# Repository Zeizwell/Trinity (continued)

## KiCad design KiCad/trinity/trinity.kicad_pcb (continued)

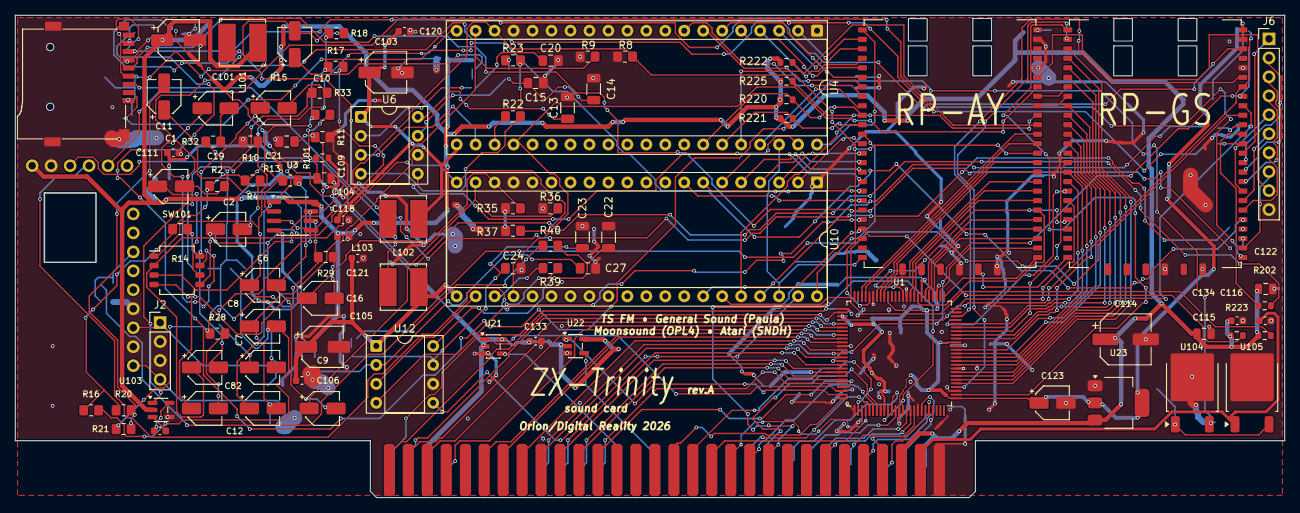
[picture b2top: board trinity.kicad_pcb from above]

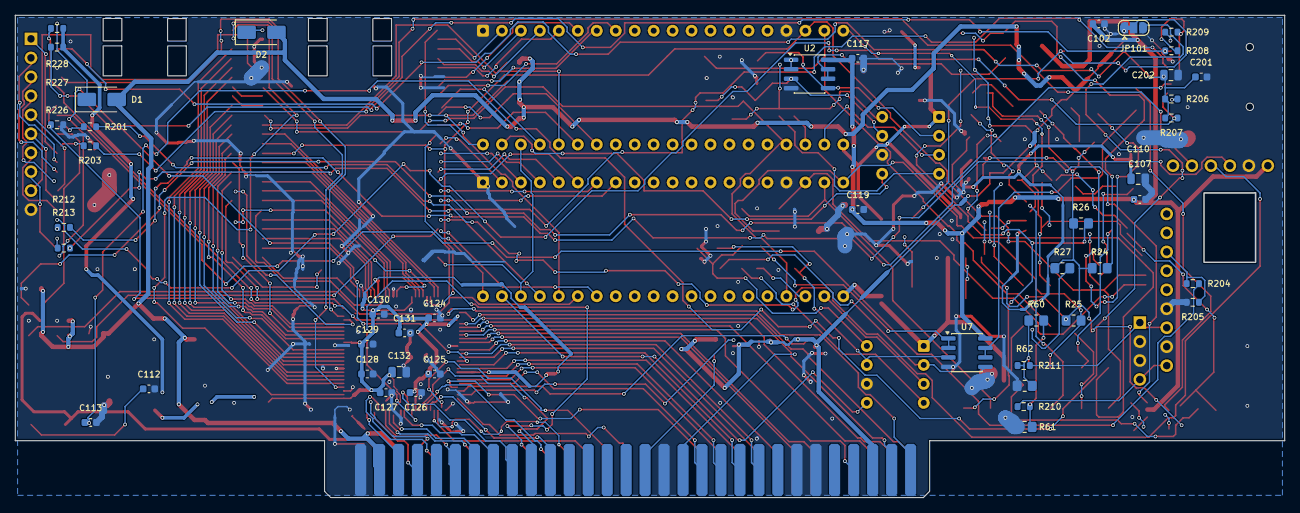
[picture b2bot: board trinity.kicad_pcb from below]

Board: 2 copper layers, 170.0 x 64.6 mm, 142 parts (45 on the bottom side), 193 nets.

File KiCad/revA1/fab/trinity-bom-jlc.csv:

Comment,Designator,Footprint,LCSC
10u,"C1,C2,C6,C7,C8,C9,C10,C11,C12,C16,C19,C21,C82,C83",CP_Elec_4x5.4,C213487
47u,"C101,C103,C105",CP_Elec_5x5.4,C72515
100n,"C102,C117,C119,C124,C125,C126,C127,C128,C129,C130,C131,C201,C104,C106,C111,C118,C120,C121,C133,C134",C_0603_1608Metric,C14663
2.2u,C107,C_0603_1608Metric,C23630
1u,C108,C_0603_1608Metric,C15849
10u,"C110,C132,C202,C109,C115,C122",C_0805_2012Metric,C15850
100u/16V,C114,CP_Elec_6.3x7.7,C72476
22u,C123,CP_Elec_4x5.4,C72502
10u/16V X5R,"C13,C14,C22,C23",C_1206_3216Metric,C13585
2.2n,"C20,C27",C_0805_2012Metric_Pad1.18x1.45mm_HandSolder,C28260
100n,"C4,C15,C24",C_0805_2012Metric_Pad1.18x1.45mm_HandSolder,C49678
SS14,"D1,D2",D_SMA,C2480
27u,"L101,L102,L103",L_Bourns_SRN6045TA,C168081
10,R101,R_0603_1608Metric,C22859
0,R11,R_0805_2012Metric_Pad1.20x1.40mm_HandSolder,C17477
24k,"R13,R14,R28,R29",R_0805_2012Metric_Pad1.20x1.40mm_HandSolder,C17575
82k,"R2,R4,R32,R33",R_0805_2012Metric_Pad1.20x1.40mm_HandSolder,C17840
33,"R201,R203,R212,R213,R202",R_0603_1608Metric,C23140
1k,"R204,R210,R211,R226",R_0603_1608Metric,C21190
10k,"R206,R207,R208,R209,R227,R228,R220,R221,R222,R223,R224,R225",R_0603_1608Metric,C25804
1k,"R22,R39",R_0805_2012Metric_Pad1.20x1.40mm_HandSolder,C17513
470,"R23,R40",R_0805_2012Metric_Pad1.20x1.40mm_HandSolder,C17710
10k,"R24,R18,R20,R21",R_0805_2012Metric_Pad1.20x1.40mm_HandSolder,C17414
10K,"R25,R60,R15",R_0805_2012Metric_Pad1.20x1.40mm_HandSolder,C17414
47k,"R26,R27,R61,R62,R16,R17",R_0805_2012Metric_Pad1.20x1.40mm_HandSolder,C17713
3.3k,"R8,R9,R10,R35,R36,R37",R_0805_2012Metric_Pad1.20x1.40mm_HandSolder,C26010
NARROW,SW101,SW_DIP_SPSTx04_Slide_Omron_A6H-4101_W6.15mm_P1.27mm,C397291
TPS60400,U103,SOT-23-5,C9839
LM358D,"U2,U7",SOIC-8_3.9x4.9mm_P1.27mm,C7950
74LVC1G125,"U21,U22",SOT-23-5,C23654
AMS1117-3.3,U23,SOT-223-3_TabPin2,C6186
NJM4580,U3,SOIC-8_3.9x4.9mm_P1.27mm,C3000516

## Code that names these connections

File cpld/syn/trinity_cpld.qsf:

# Ножки - из KiCad/trinity/gen/cpld_gen.py
set_global_assignment -name FAMILY MAX3000A
set_global_assignment -name DEVICE "EPM3128ATC100-10"
set_global_assignment -name TOP_LEVEL_ENTITY trinity_cpld
set_global_assignment -name VERILOG_FILE ../rtl/top.v
set_global_assignment -name SDC_FILE clocks.sdc
set_global_assignment -name MAX7000_DEVICE_IO_STANDARD "3.3-V LVTTL"
set_global_assignment -name RESERVE_ALL_UNUSED_PINS "AS INPUT TRI-STATED"
set_location_assignment PIN_87 -to clk
set_location_assignment PIN_13 -to a[0]
set_location_assignment PIN_16 -to a[1]
set_location_assignment PIN_19 -to a[2]
set_location_assignment PIN_21 -to a[3]
set_location_assignment PIN_40 -to a[4]
set_location_assignment PIN_37 -to a[5]
set_location_assignment PIN_36 -to a[6]
set_location_assignment PIN_32 -to a[7]
set_location_assignment PIN_44 -to a[8]
set_location_assignment PIN_45 -to a[9]
set_location_assignment PIN_46 -to a[10]
set_location_assignment PIN_47 -to a[11]
set_location_assignment PIN_5 -to a[12]
set_location_assignment PIN_6 -to a[13]
set_location_assignment PIN_1 -to a[14]
set_location_assignment PIN_2 -to a[15]
set_location_assignment PIN_9 -to d[0]
set_location_assignment PIN_10 -to d[1]
set_location_assignment PIN_12 -to d[2]
set_location_assignment PIN_20 -to d[3]
set_location_assignment PIN_22 -to d[4]
set_location_assignment PIN_17 -to d[5]
set_location_assignment PIN_14 -to d[6]
set_location_assignment PIN_7 -to d[7]
set_location_assignment PIN_8 -to n_dos
set_location_assignment PIN_23 -to n_iorqge
set_location_assignment PIN_24 -to n_csromce_oe
set_location_assignment PIN_25 -to n_mreq
set_location_assignment PIN_27 -to n_iorq
set_location_assignment PIN_28 -to n_rd
set_location_assignment PIN_29 -to n_wr
set_location_assignment PIN_30 -to n_rst
set_location_assignment PIN_31 -to n_iodos
set_location_assignment PIN_35 -to n_wait
set_location_assignment PIN_41 -to n_m1
set_location_assignment PIN_42 -to csrom
set_location_assignment PIN_52 -to gs_c[0]
set_location_assignment PIN_54 -to gs_c[1]
set_location_assignment PIN_55 -to gs_c[2]
set_location_assignment PIN_56 -to gs_c[3]
set_location_assignment PIN_57 -to gs_c[4]
set_location_assignment PIN_58 -to gs_c[5]
set_location_assignment PIN_60 -to gs_wr
set_location_assignment PIN_61 -to gs_d[0]
set_location_assignment PIN_63 -to gs_d[1]
set_location_assignment PIN_64 -to gs_d[2]
set_location_assignment PIN_67 -to gs_d[3]
set_location_assignment PIN_68 -to gs_d[4]
set_location_assignment PIN_69 -to gs_d[5]
set_location_assignment PIN_70 -to gs_d[6]
set_location_assignment PIN_71 -to gs_d[7]
set_location_assignment PIN_72 -to gs_rd
set_location_assignment PIN_75 -to gs_rdy
set_location_assignment PIN_76 -to ay_d[0]
set_location_assignment PIN_77 -to ay_d[1]
set_location_assignment PIN_79 -to ay_d[2]
set_location_assignment PIN_80 -to ay_d[3]
set_location_assignment PIN_81 -to ay_d[4]
set_location_assignment PIN_83 -to ay_d[5]
set_location_assignment PIN_84 -to ay_d[6]
set_location_assignment PIN_85 -to ay_d[7]
set_location_assignment PIN_92 -to ay_wr
set_location_assignment PIN_93 -to ay_rd
set_location_assignment PIN_94 -to ay_c[0]
set_location_assignment PIN_96 -to ay_c[1]
set_location_assignment PIN_97 -to ay_rdy
set_location_assignment PIN_98 -to ay_rst

set_global_assignment -name LAST_QUARTUS_VERSION "13.0 SP1"
set_global_assignment -name RESERVE_ALL_UNUSED_PINS_NO_OUTPUT_GND "AS INPUT TRI-STATED"

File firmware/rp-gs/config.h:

// Ножки RP-GS (значения настроек - gs_cfg). На макете шина - слот YM: A0 = 1 порт #B3, A0 = 0 порт #BB. На рев А ножки другие
#ifndef CONFIG_H
#define CONFIG_H

#define FW_VERSION 1            // версия прошивки: поднимать при выпуске, драйвер показывает

#ifdef BOARD_REV_A
// Плата рев А: KiCad/trinity/gen/gs_gen.py
#define PIN_GS_C0   0           // код порта от CPLD, GP0..GP5
#define PIN_GS_WR   8
#define PIN_GS_D0   9           // данные, GP9..GP16
#define PIN_GS_RD   17
#define PIN_GS_RDY  18
#define PIN_CPLD_CLK 21

#define PIN_BCK  40
#define PIN_LCK  41             // сразу за BCK
#define PIN_DIN  42
#define PIN_XSMT 43
#else
#define PIN_SLOT_D0 0           // D0..D7 = GP0..GP7
#define PIN_SLOT_CS 8
#define PIN_SLOT_WR 9
#define PIN_SLOT_RD 10
#define PIN_SLOT_A0 11

// I2S: doc/zx-trinity.md, «PCM5102A на макете»
#define PIN_DIN 14
#define PIN_BCK 15
#define PIN_LCK 16              // сразу за BCK
#endif

// SD: рев А, SPI1 (trinity-board-checklist). На макете эти ножки - шина слота, трогать нельзя
#define BOARD_HAS_SD 0
#define PIN_SD_MISO 28
#define PIN_SD_CS   29
#define PIN_SD_SCK  30
#define PIN_SD_MOSI 31
#define PIN_SD_DET  32

#endif

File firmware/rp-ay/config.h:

// Настройки RP-AY - ВСЁ, что может понадобиться подкрутить, здесь, одной структурой (cfg).
// Код читает только cfg, сам чисел не держит. Сейчас - заводские значения (cfg_defaults);
// потом - из флеша и командой со Спектрума (пакет CFG), без правки кода.
// Решения - doc/zx-trinity.md, раздел 14а.
#pragma once

// Версия прошивки: +1 на каждую сборку, что идёт в RP. build.bat кладёт файл в bin/rp_ay_vNN.uf2 и старые не трогает
#define FW_VERSION      64
#include <stdint.h>
#include <stdbool.h>

#ifdef BOARD_REV_A
// ---- Ножки платы рев А (doc/trinity-board-checklist.md, KiCad/trinity/gen/rpay_gen.py)
#define PIN_AY_D0    28  // шина к CPLD: данные GP28..GP35
#define PIN_AY_WR    36
#define PIN_AY_RD    37
#define PIN_AY_C0    38  // код порта: GP38, GP39
#define PIN_AY_RDY   40
#define PIN_AY_RST   41  // от CPLD, 1 - сброс
#define PIN_CHIP_IC  46  // /IC обоих чипов
#define PIN_PHIM     25  // такт чипов, CLK_GPOUT3
#define PIN_SLOT_PHIM PIN_PHIM   // замер такта (phim_khz) - свой же
#define PIN_RGB      20
#define CHIP_N       2
//                       D0, A0, /CS, /WR, /RD
#define CHIP_PIN_TABLE { { 0, 8, 9, 10, 42 }, { 11, 21, 22, 23, 43 } }
#else
// ---- Ножки макета (doc/zx-trinity.md, п.15). На плате - другие: менять ТОЛЬКО здесь (C и PIO берут отсюда).
// Требование к разводке: D0..D7 слота подряд, D0..D7 чипа подряд; остальные - любые (слот - в окне 32 ножек PIO).
#define PIN_SLOT_D0     0   // слот: D0..D7 = GP0..GP7 (RP выдаёт только на чтение своего чипа)
#define PIN_SLOT_CS     8   // /CS чипа (/YM1_CS)
#define PIN_SLOT_WR     9   // /WR (/AWR)
#define PIN_SLOT_RD     10  // /RD (/ARD)
#define PIN_SLOT_A0     11  // A0 (AA0)
#define PIN_SLOT_PHIM   12  // такт чипа из слота (φM) - на макете RP его только слушает
#define PIN_SLOT_IC     13  // /IC - сброс
#define PIN_CHIP_D0     28  // в чип: D0..D7 = GP28..GP35
#define PIN_CHIP_CS     36
#define PIN_CHIP_WR     37
#define PIN_CHIP_A0     38
#define PIN_CHIP_RD     39  // /RD чипа - только для теста (режим TEST); на чипе подтяжка 10к к +5 В
#define PIN_RGB         20  // светодиод WS2812 на Spotpear
#define CHIP_N          1
#define CHIP_PIN_TABLE  { { PIN_CHIP_D0, PIN_CHIP_A0, PIN_CHIP_CS, PIN_CHIP_WR, PIN_CHIP_RD } }
#endif

// ---- PSRAM 8 МБ (psram.h): пул временных слотов служебного API (doc/trinity-api.md) - с начала
#define SVC_POOL_KB     128
#define PSRAM_SVC       0
#define PSRAM_ATARI     (1u << 20)      // машина Atari самоплеера (sndh_arena): 4 МБ RAM, файл, распаковка
#define PSRAM_ATARI_SIZE (7u << 20)

// ---- Режимы (doc 14а). Порядок - как в таблице переходов modes.c
typedef enum { MODE_AY, MODE_FX, MODE_ATARI, MODE_UPDATE, MODE_TEST, MODE_COUNT } mode_t;

typedef struct {
    // --- чип: тайминги записи - как у Z80 на 3.5 МГц (в этом ритме чипы работали всегда); в ПОЛУтактах Z80
    uint32_t z80_hz;            // такт Z80, от которого считаем (3.5 МГц: такт 286 нс)
    uint8_t  setup_ht;          // данные и A0 -> /WR вниз (Z80: ~1 такт, с T1)
    uint8_t  pulse_ht;          // длительность /WR (Z80, цикл ввода-вывода: T2 + TW + полтакта T3 = 2.5 такта)
    uint8_t  hold_ht;           // /WR вверх -> /CS вверх (Z80: /WR - на спаде T3, адрес до следующего T1 = полтакта)
    uint8_t  gap_addr_ht;       // после записи адреса до данных (Z80: OUT адреса -> LD B,n -> OUT данных, ~11 тактов)
    uint8_t  gap_ssg_ht;        // после данных в регистр 0..15 до следующей записи (так же)
    uint32_t phim_hz;           // такт чипа, Гц (для паузы FM - в тактах чипа)
    uint16_t wait_fm_clk;       // после данных в регистр FM (YM2203: 83 такта чипа; Z80 ждёт флаг занятости, RP - сама)
    uint16_t rd_pulse_ns;       // тест: /RD вниз -> читаем данные
    uint8_t  timing_preset;     // паузы: 0 - default (ритм Z80, 100 %), 1 - tuned (tuned_pct, из теста пауз)
    uint16_t tuned_pct[5];      // tuned: % ритма Z80 - установка, /WR, удержание, после адреса, после данных
    uint8_t  timing_margin_pct; // тест пауз: рабочее = минимум без ошибок + столько %
    // --- ответ на чтение со стороны Спектрума
    uint8_t  status_answer;     // чтение A0 = 0 (статус YM2203): 0 - никогда не занят
    // --- режимы
    mode_t   mode_after_reset;  // режим после сброса (/IC) и включения
    bool     silence_on_reset;  // после сброса - тишина в чип (громкости 0)
    uint16_t boot_beep_ms;      // при включении RP сама играет ноту в канал A, мс (0 - нет): проверка RP -> чип
    bool     boot_test;         // при включении - тест чтения чипа (/RD -> GP39), итог светодиодом 5 с
    uint16_t fx_timeout_s;      // FX: нет пакетов и записей столько секунд - эффекты выкл (0 - никогда)
    uint8_t  chips;             // чипов: 2 - RP сама выбирает чип по #FE / #FF (плата); 1 - выбор не её (макет за CPLD)
    // --- AY FX (таймерные эффекты, движок engine/ayfx.c)
    uint32_t ay_clock_hz;       // такт AY для таймеров эффектов: такт тона = ay_clock_hz / 8
    uint8_t  frame_hz;          // кадр для свипа ШИМ, Гц (0 - свипа нет)
    // --- RP
    uint32_t sys_khz;           // такт RP, кГц (150000 - штатный)
    int      vreg;              // напряжение ядра (VREG_VOLTAGE_*), под такт
    // --- служебное
    uint8_t  led_bright;        // яркость светодиода 0..255
    uint16_t log_period_ms;     // счётчики в USB-консоль, мс (0 - не писать)
} cfg_t;

extern cfg_t cfg;
void cfg_defaults(void);
